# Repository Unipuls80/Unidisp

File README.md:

# Unidisp
Výrobní podklady pro univerzální displej s digitrony, obstarávající napájení a buzení.

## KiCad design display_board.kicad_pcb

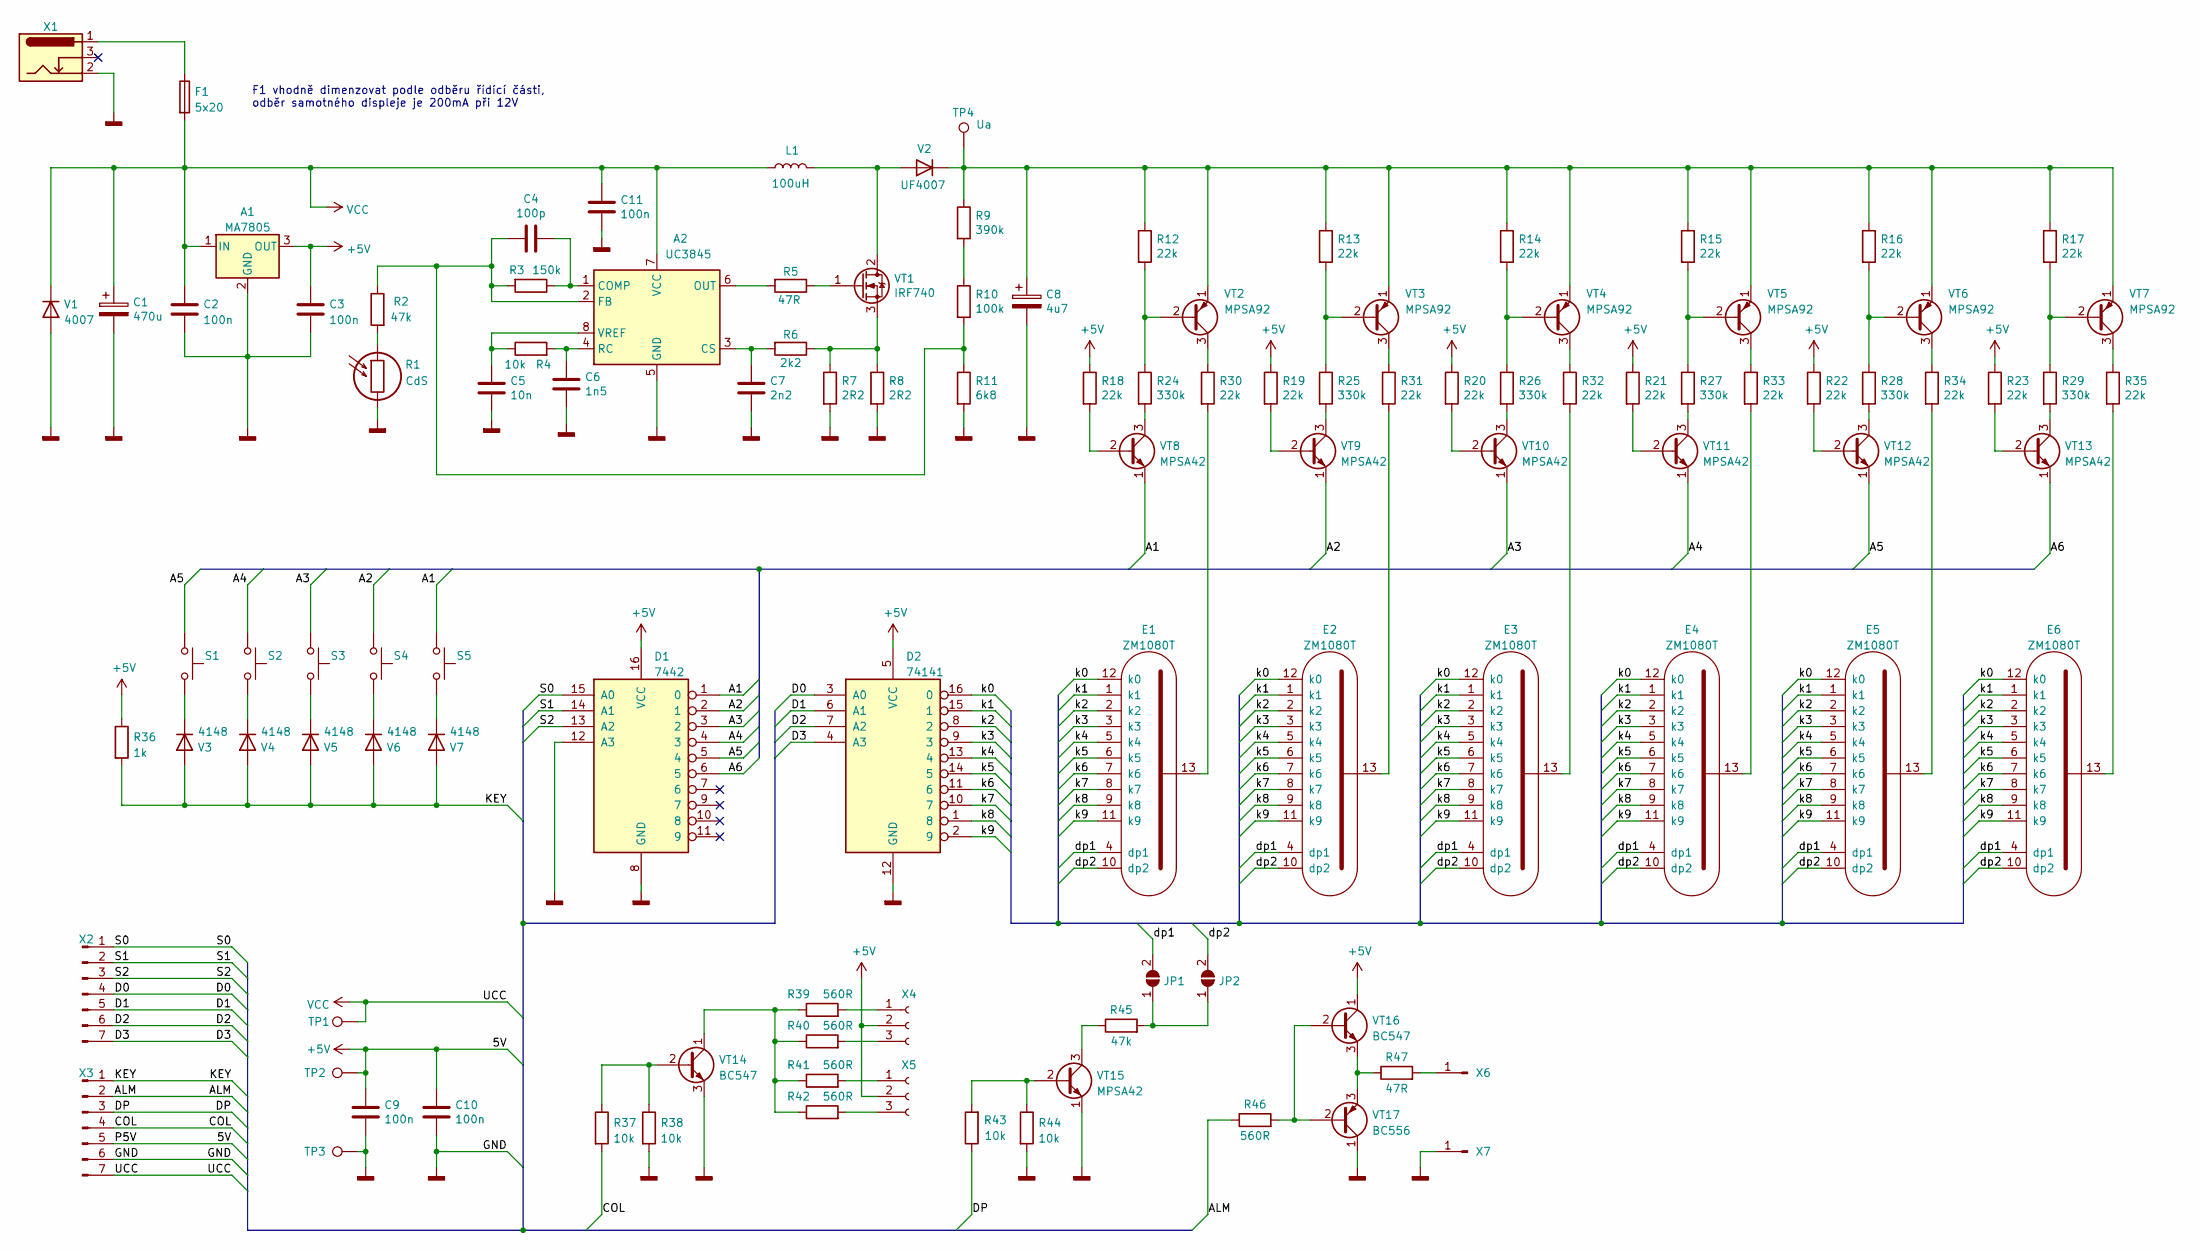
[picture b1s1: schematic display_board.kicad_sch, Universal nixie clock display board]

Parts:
A1: MA7805; TO-3_78xx
A2: UC3845; DIP-8_W7.62mm
C1: 470u; CP_Radial_D8.0mm_P3.80mm
C2, C3, C9, C10, C11: 100n; C_Disc_D4.3mm_W1.9mm_P5.00mm
C4: 100p; C_Disc_D4.3mm_W1.9mm_P5.00mm
C5: 10n; C_Disc_D4.3mm_W1.9mm_P5.00mm
C6: 1n5; C_Disc_D4.3mm_W1.9mm_P5.00mm
C7: 2n2; C_Disc_D4.3mm_W1.9mm_P5.00mm
C8: 4u7; CP_Radial_D10.0mm_P3.80mm
D1: 7442; DIP-16_W7.62mm
D2: 74141; DIP-16_W7.62mm
E1, E2, E3, E4, E5, E6: ZM1080T; nixie_13pin
F1: 5x20; Fuseholder_Cylinder-5x20mm_Stelvio-Kontek_PTF76_Horizontal_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
JP1, JP2: SolderJumper_2_Open; SolderJumper-2_P1.3mm_Open_Pad1.0x1.5mm
L1: 100uH; L_Radial_D8.7mm_P5.00mm_Fastron_07HCP
R1: CdS; R_LDR_D6.4mm_P3.4mm_Vertical
R2, R45: 47k; R DIN0207 10.16mm
R3: 150k; R DIN0207 10.16mm
R4, R37, R38, R43, R44: 10k; R DIN0207 10.16mm
R5, R47: 47R; R DIN0207 10.16mm
R6: 2k2; R DIN0207 10.16mm
R7, R8: 2R2; R DIN0207 10.16mm
R9: 390k; R DIN0207 10.16mm
R10: 100k; R DIN0207 10.16mm
R11: 6k8; R DIN0207 10.16mm
R12, R13, R14, R15, R16, R17, R18, R19, R20, R21, R22, R23, R30, R31, R32, R33, R34, R35: 22k; R DIN0207 10.16mm
R24, R25, R26, R27, R28, R29: 330k; R DIN0207 10.16mm
R36: 1k; R DIN0207 10.16mm
R39, R40, R41, R42, R46: 560R; R DIN0207 10.16mm
S1, S2, S3, S4, S5: SW_Push; SW_Tactile_SPST_Angled_PTS645Vx58-2LFS
TP1: Vcc; TestPoint_THTPad_D3.0mm_Drill1.5mm
TP2: +5V; TestPoint_THTPad_D3.0mm_Drill1.5mm
TP3: GND; TestPoint_THTPad_D3.0mm_Drill1.5mm
TP4: Ua; TestPoint_THTPad_D3.0mm_Drill1.5mm
V1: 4007; D_DO-41_SOD81_P10.16mm_Horizontal
V2: UF4007; D_DO-41_SOD81_P10.16mm_Horizontal
V3, V4, V5, V6, V7: 4148; D_DO-35_SOD27_P10.16mm_Horizontal
VT1: IRF740; TO-220-3_Horizontal_TabDown
VT2, VT3, VT4, VT5, VT6, VT7: MPSA92; TO-92_Wide
VT8, VT9, VT10, VT11, VT12, VT13, VT15: MPSA42; TO-92_Wide
VT14, VT16: BC547; TO-92_Wide
VT17: BC556; TO-92_Wide
X1: Barrel_Jack_Switch; BarrelJack_Horizontal
X2, X3: Conn_01x07_Male; PinHeader_1x07_P2.54mm_Vertical
X4, X5: Conn_01x03_Female; PinSocket_1x03_P2.54mm_Vertical
X6, X7: Conn_01x01_Male; PinHeader_1x01_P2.54mm_Vertical

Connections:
+5V: A1.3 (OUT), C3.1, C9.1, C10.1, D1.16 (VCC), D2.5 (VCC), R18.1, R19.1, R20.1, R21.1, R22.1, R23.1, R36.1, TP2.1, VT16.1 (C), X3.5, X4.2, X5.2
/A1: D1.1 (0), S5.1, VT8.1 (E)
/A2: D1.2 (1), S4.1, VT9.1 (E)
/A3: D1.3 (2), S3.1, VT10.1 (E)
/A4: D1.4 (3), S2.1, VT11.1 (E)
/A5: D1.5 (4), S1.1, VT12.1 (E)
/A6: D1.6 (5), VT13.1 (E)
/ALM: R46.1, X3.2
/COL: R37.2, X3.4
/D0: D2.3 (A0), X2.4
/D1: D2.6 (A1), X2.5
/D2: D2.7 (A2), X2.6
/D3: D2.4 (A3), X2.7
/DP: R43.1, X3.3
/KEY: R36.2, V3.2 (A), V4.2 (A), V5.2 (A), V6.2 (A), V7.2 (A), X3.1
/S0: D1.15 (A0), X2.1
/S1: D1.14 (A1), X2.2
/S2: D1.13 (A2), X2.3
/dp1: E1.4 (dp1), E2.4 (dp1), E3.4 (dp1), E4.4 (dp1), E5.4 (dp1), E6.4 (dp1), JP1.2 (B)
/dp2: E1.10 (dp2), E2.10 (dp2), E3.10 (dp2), E4.10 (dp2), E5.10 (dp2), E6.10 (dp2), JP2.2 (B)
/k0: D2.16 (0), E1.12 (k0), E2.12 (k0), E3.12 (k0), E4.12 (k0), E5.12 (k0), E6.12 (k0)
/k1: D2.15 (1), E1.1 (k1), E2.1 (k1), E3.1 (k1), E4.1 (k1), E5.1 (k1), E6.1 (k1)
/k2: D2.8 (2), E1.2 (k2), E2.2 (k2), E3.2 (k2), E4.2 (k2), E5.2 (k2), E6.2 (k2)
/k3: D2.9 (3), E1.3 (k3), E2.3 (k3), E3.3 (k3), E4.3 (k3), E5.3 (k3), E6.3 (k3)
/k4: D2.13 (4), E1.5 (k4), E2.5 (k4), E3.5 (k4), E4.5 (k4), E5.5 (k4), E6.5 (k4)
/k5: D2.14 (5), E1.6 (k5), E2.6 (k5), E3.6 (k5), E4.6 (k5), E5.6 (k5), E6.6 (k5)
/k6: D2.11 (6), E1.7 (k6), E2.7 (k6), E3.7 (k6), E4.7 (k6), E5.7 (k6), E6.7 (k6)
/k7: D2.10 (7), E1.8 (k7), E2.8 (k7), E3.8 (k7), E4.8 (k7), E5.8 (k7), E6.8 (k7)
/k8: D2.1 (8), E1.9 (k8), E2.9 (k8), E3.9 (k8), E4.9 (k8), E5.9 (k8), E6.9 (k8)
/k9: D2.2 (9), E1.11 (k9), E2.11 (k9), E3.11 (k9), E4.11 (k9), E5.11 (k9), E6.11 (k9)
GNDD: A1.2 (GND), A2.5 (GND), C1.2, C2.2, C3.2, C5.2, C6.2, C7.2, C8.2, C9.2, C10.2, C11.2, D1.8 (GND), D1.12 (A3), D2.12 (GND), R1.2, R7.2, R8.2, R11.2, R38.2, R44.2, TP3.1, V1.2 (A), VT14.3 (E), VT15.1 (E), VT17.1 (C), X1.2, X3.6, X7.1
unnamed: A2.1 (COMP), C4.1, R3.1
unnamed: A2.2 (FB), C4.2, R2.1, R3.2, R10.2, R11.1
unnamed: A2.3 (CS), C7.1, R6.2
unnamed: A2.4 (RC), C6.1, R4.2
unnamed: A2.6 (OUT), R5.2
unnamed: A2.8 (VREF), C5.1, R4.1
unnamed: C8.1, R9.1, R12.1, R13.1, R14.1, R15.1, R16.1, R17.1, TP4.1, V2.1 (K), VT2.1 (E), VT3.1 (E), VT4.1 (E), VT5.1 (E), VT6.1 (E), VT7.1 (E)
unnamed: E1.13, R30.2
unnamed: E2.13, R31.2
unnamed: E3.13, R32.2
unnamed: E4.13, R33.2
unnamed: E5.13, R34.2
unnamed: E6.13, R35.2
unnamed: F1.1, X1.1
unnamed: JP1.1 (A), JP2.1 (A), R45.2
unnamed: L1.2, V2.2 (A), VT1.2 (D)
unnamed: R1.1, R2.2
unnamed: R5.1, VT1.1 (G)
unnamed: R6.1, R7.1, R8.1, VT1.3 (S)
unnamed: R9.2, R10.1
unnamed: R12.2, R24.1, VT2.2 (B)
unnamed: R13.2, R25.1, VT3.2 (B)
unnamed: R14.2, R26.1, VT4.2 (B)
unnamed: R15.2, R27.1, VT5.2 (B)
unnamed: R16.2, R28.1, VT6.2 (B)
unnamed: R17.2, R29.1, VT7.2 (B)
unnamed: R18.2, VT8.2 (B)
unnamed: R19.2, VT9.2 (B)
unnamed: R20.2, VT10.2 (B)
unnamed: R21.2, VT11.2 (B)
unnamed: R22.2, VT12.2 (B)
unnamed: R23.2, VT13.2 (B)
unnamed: R24.2, VT8.3 (C)
unnamed: R25.2, VT9.3 (C)
unnamed: R26.2, VT10.3 (C)
unnamed: R27.2, VT11.3 (C)
unnamed: R28.2, VT12.3 (C)
unnamed: R29.2, VT13.3 (C)
unnamed: R30.1, VT2.3 (C)
unnamed: R31.1, VT3.3 (C)
unnamed: R32.1, VT4.3 (C)
unnamed: R33.1, VT5.3 (C)
unnamed: R34.1, VT6.3 (C)
unnamed: R35.1, VT7.3 (C)
unnamed: R37.1, R38.1, VT14.2 (B)
unnamed: R39.1, R40.1, R41.1, R42.1, VT14.1 (C)
unnamed: R39.2, X4.1
unnamed: R40.2, X4.3
unnamed: R41.2, X5.1
unnamed: R42.2, X5.3
unnamed: R43.2, R44.1, VT15.2 (B)
unnamed: R45.1, VT15.3 (C)
unnamed: R46.2, VT16.2 (B), VT17.2 (B)
unnamed: R47.1, VT16.3 (E), VT17.3 (E)
unnamed: R47.2, X6.1
unnamed: S1.2, V3.1 (K)
unnamed: S2.2, V4.1 (K)
unnamed: S3.2, V5.1 (K)
unnamed: S4.2, V6.1 (K)
unnamed: S5.2, V7.1 (K)
VCC: A1.1 (IN), A2.7 (VCC), C1.1, C2.1, C11.1, F1.2, L1.1, TP1.1, V1.1 (K), X3.7

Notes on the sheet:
F1 vhodně dimenzovat podle odběru řídící části, odběr samotného displeje je 200mA při 12V

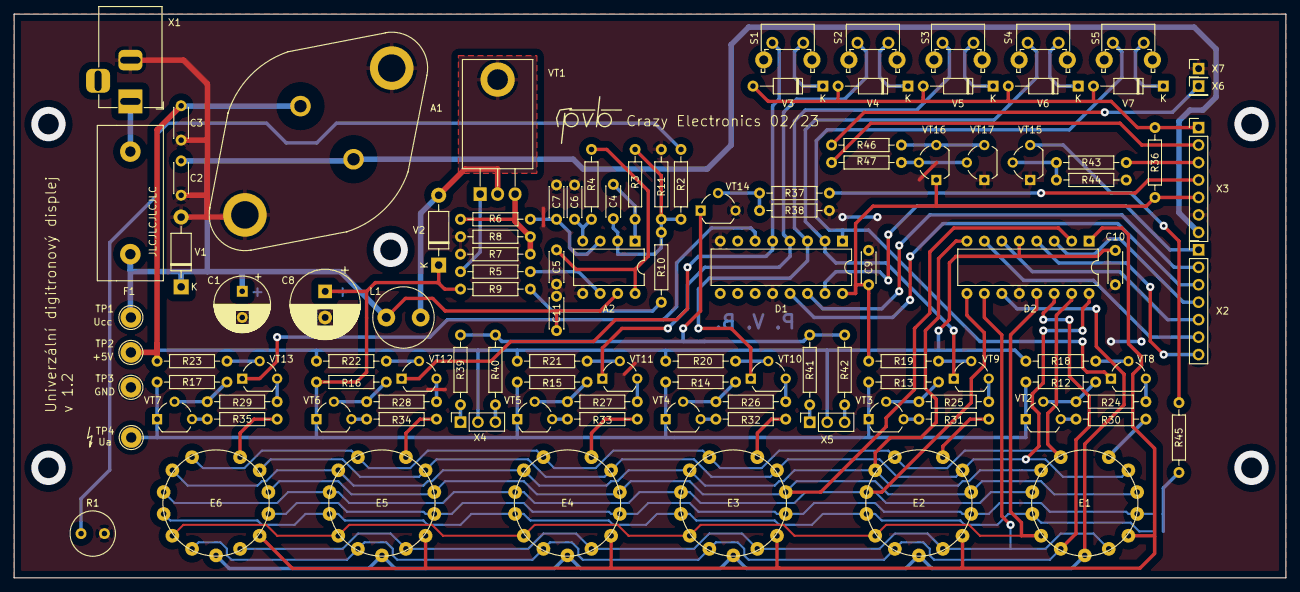
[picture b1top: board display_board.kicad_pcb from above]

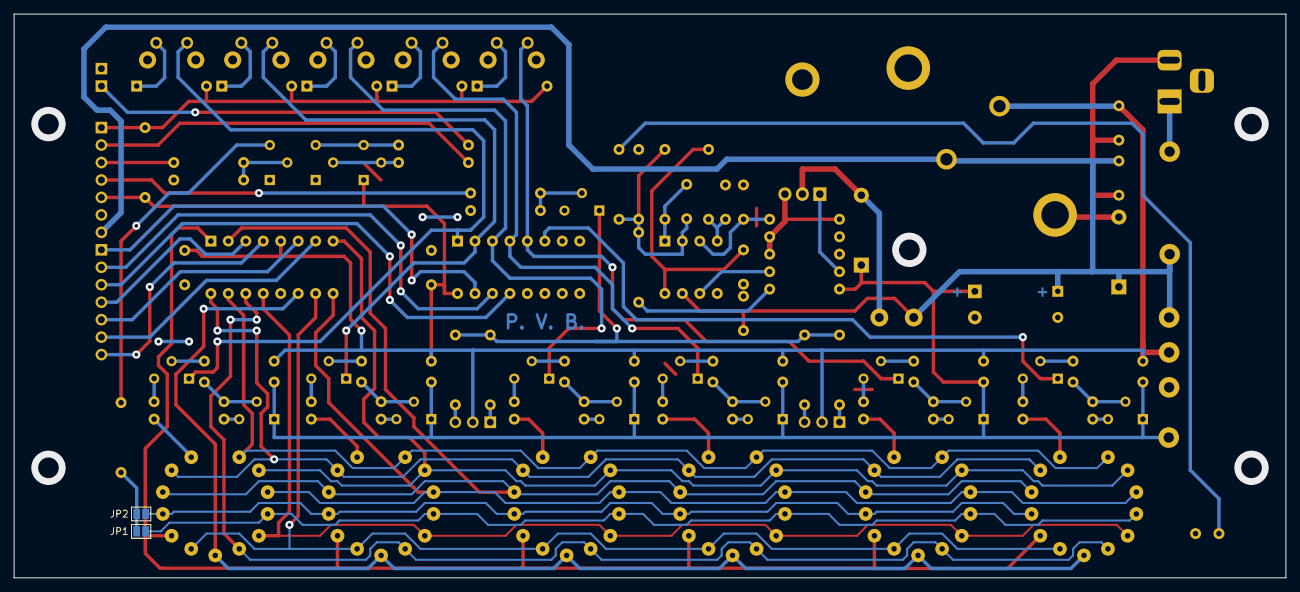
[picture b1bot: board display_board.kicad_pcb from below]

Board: 2 copper layers, 185.0 x 82.0 mm, 112 parts (2 on the bottom side), 92 nets.

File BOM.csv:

Indukčnosti;;
L1;100uH 2A pp. 50kHz;radiální
;;
Rezistory ;;
R1;CdS 5mm;-
R2, R45;47k 5% ;R0207
R3;150k 5% ;R0207
R4;10k 1%;R0207
R5, R47;47R 5%;R0207
R6;2k2 5%;R0207
R7, R8;2R2 5%;R0207
R9;390k 1%;R0207
R10;100k 1%;R0207
R11 ;6k8 1%;R0207
R12 .. R23;22k 5%;R0207
R30 .. R35;;
R24 .. R29;330k 5%;R0207
R36;1k 5%;R0207
R37, R38;10k 5%;R0207
R43, R44;;
R39 .. R42, R46;560R 5%;R0207
;;
Kondenzátory;;
C1;470uF 16V ;elektrol. radiální
C2, C3, C9;100n 16V;keramický
C10, C11;;
C4;100p 16V ;keramický
C5;10n 16V ;keramický
C6 ;1n5 16V ;keramický
C7;2n2 16V ;keramický
C8;4,7uF 250V ;elektrol. radiální
;;
Diody;;
V1;1N4007;-
V2;UF4007;-
V3..V7;1N4148;-
;;
Tranzistory;;
VT1;IRF740;upevnit k DPS
VT2..VT7;MPSA92;-
VT8..VT13, VT15;MPSA42;-
VT14, VT16;BC547 ;-
VT17;BC556 ;-
;;
Integrované obvody;;
A1;MA7805;upevnit k DPS
A2;UC3845;-
D1;74x42;-
D2;74x141;-
;;
Výbojky;;
E1..E6;Z57xM, ZM1080(T) a ekvivalentní;
;;
Konektory;;
X1;zdířka souosá;5,5mm/2,1mm
X2..X7;hřeben, samec;2,54mm
;;
Pojistky;;
F1;podle celk. odběru;5x20mm
pouzdro pro F1;PTF76 ;15mm rozteč

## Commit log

2023-02-06 Create Theory Of Operation
2023-02-11 Create LICENSE
